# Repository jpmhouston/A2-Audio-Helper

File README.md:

This is a potential Apple II hardware mod I hope to eventually turn into a working physical add-on for any ][, ][+, //e. It’s meant to add these capabilities:

- route sound card audio to the stock speaker
- mixing motherboard audio into the sound card audio (i believe some sound cards don’t come with this feature)
- an optional second speaker mounted into the case for stereo (mounting strategy not determined yet)
- control volume with a knob protruding through a hole dremel'd into case beneath the keyboard (willing to accept feedback about an alternate volume control and placement, of if volume control should be made optional)
- when volume knob turned off, output to a line-out jack at the back of the case (attached to one of those mounts for a //e, not sure what yet for older ][’s)
- output to headphone jack at the back of the case, also controlled by the volume knob, disabling the speaker(s) when connected (also attached to one of those mounts for a //e, maybe both jacks out one wide slot)
- optionally output to another headphone jack at the front of the case (via a second hole in the case beside the volume knob)

These features should be possible using a small circuit board to be mounted within the case beneath the keyboard with some minor modifications, either one or two holes drilled into the case's metal base, the part that's angled upwards. It should require no controller or firmware, and the plan is to connect it to power and ground via the motherboard’s game port (potentially using a pass-through socket to permit its use for joysticks or whatever else). 

The schematic originates from a specification fed to Gemini and a KiCad project created according to its design, making use of a 8403 amplifier module. Needless to say there were numerous back and forth sessions. I created a simple PCB design as a proof of concept, currently all through-hole components. Well it leverages a ready-to-use amplifier module with its own surface-mount components, but that itself needs connection with pin headers.

The latest iteration of the PCB is 4.5cm wide and 6.3cn tall, and I'm hoping they will fit, on a //e between the motherboard and the end of the flat part of the base, somewhat in the center or right of the case. On a ][ / ][+ I'm hoping there's room in front of the power supply. I know the stock speaker is in that area, I'll have to see more 2's in the wild and see. For both models there should also be space at the far right side of the vents for an second speaker to be mounted somehow.

Volume and front headphone are on a small daughterboard, connected via a ribbon cable, that can mount flush to the upwardly angled part of the base, I'm hoping there's room directly under the keyboard at this angle and still allow the knob and jack to be high enough off the table to be useful. The main board however is also able to have the volume and headphone jack populated on it directly instead, for those wanting to mount it with those controls protruding out the side of the case. I'm making it support this just for me really, as my own case if damaged and I don't mind making holes in the beige plastic, and especially if I run into space issues under the keybaord. I suspect this option will be less of an interest to others since making holes in the beige plastic is not something they'd want to do, and not something I'd recommend.

I also am planning how to mount line-out and optionally a second headphone jack to the back of the case. I've found what might be good jack components, and I think they'll work in one of the long //e openings, but not sure yet. I suspect some 3D-printed thing will be involved in making this work.

I'm putting the cart before the horse a bit iterating over the PCB layout and pondering these physical issues, as I’ve still yet to test an implementation of the schematic on a breadboard.

Feedback and assistance are appreciated on the Discussions page for this repo, especially feedback on the schematic and PCB since I really a beginner in all this. Especially feedback on the physical mounting and modding challenges for this thing. Thanks.

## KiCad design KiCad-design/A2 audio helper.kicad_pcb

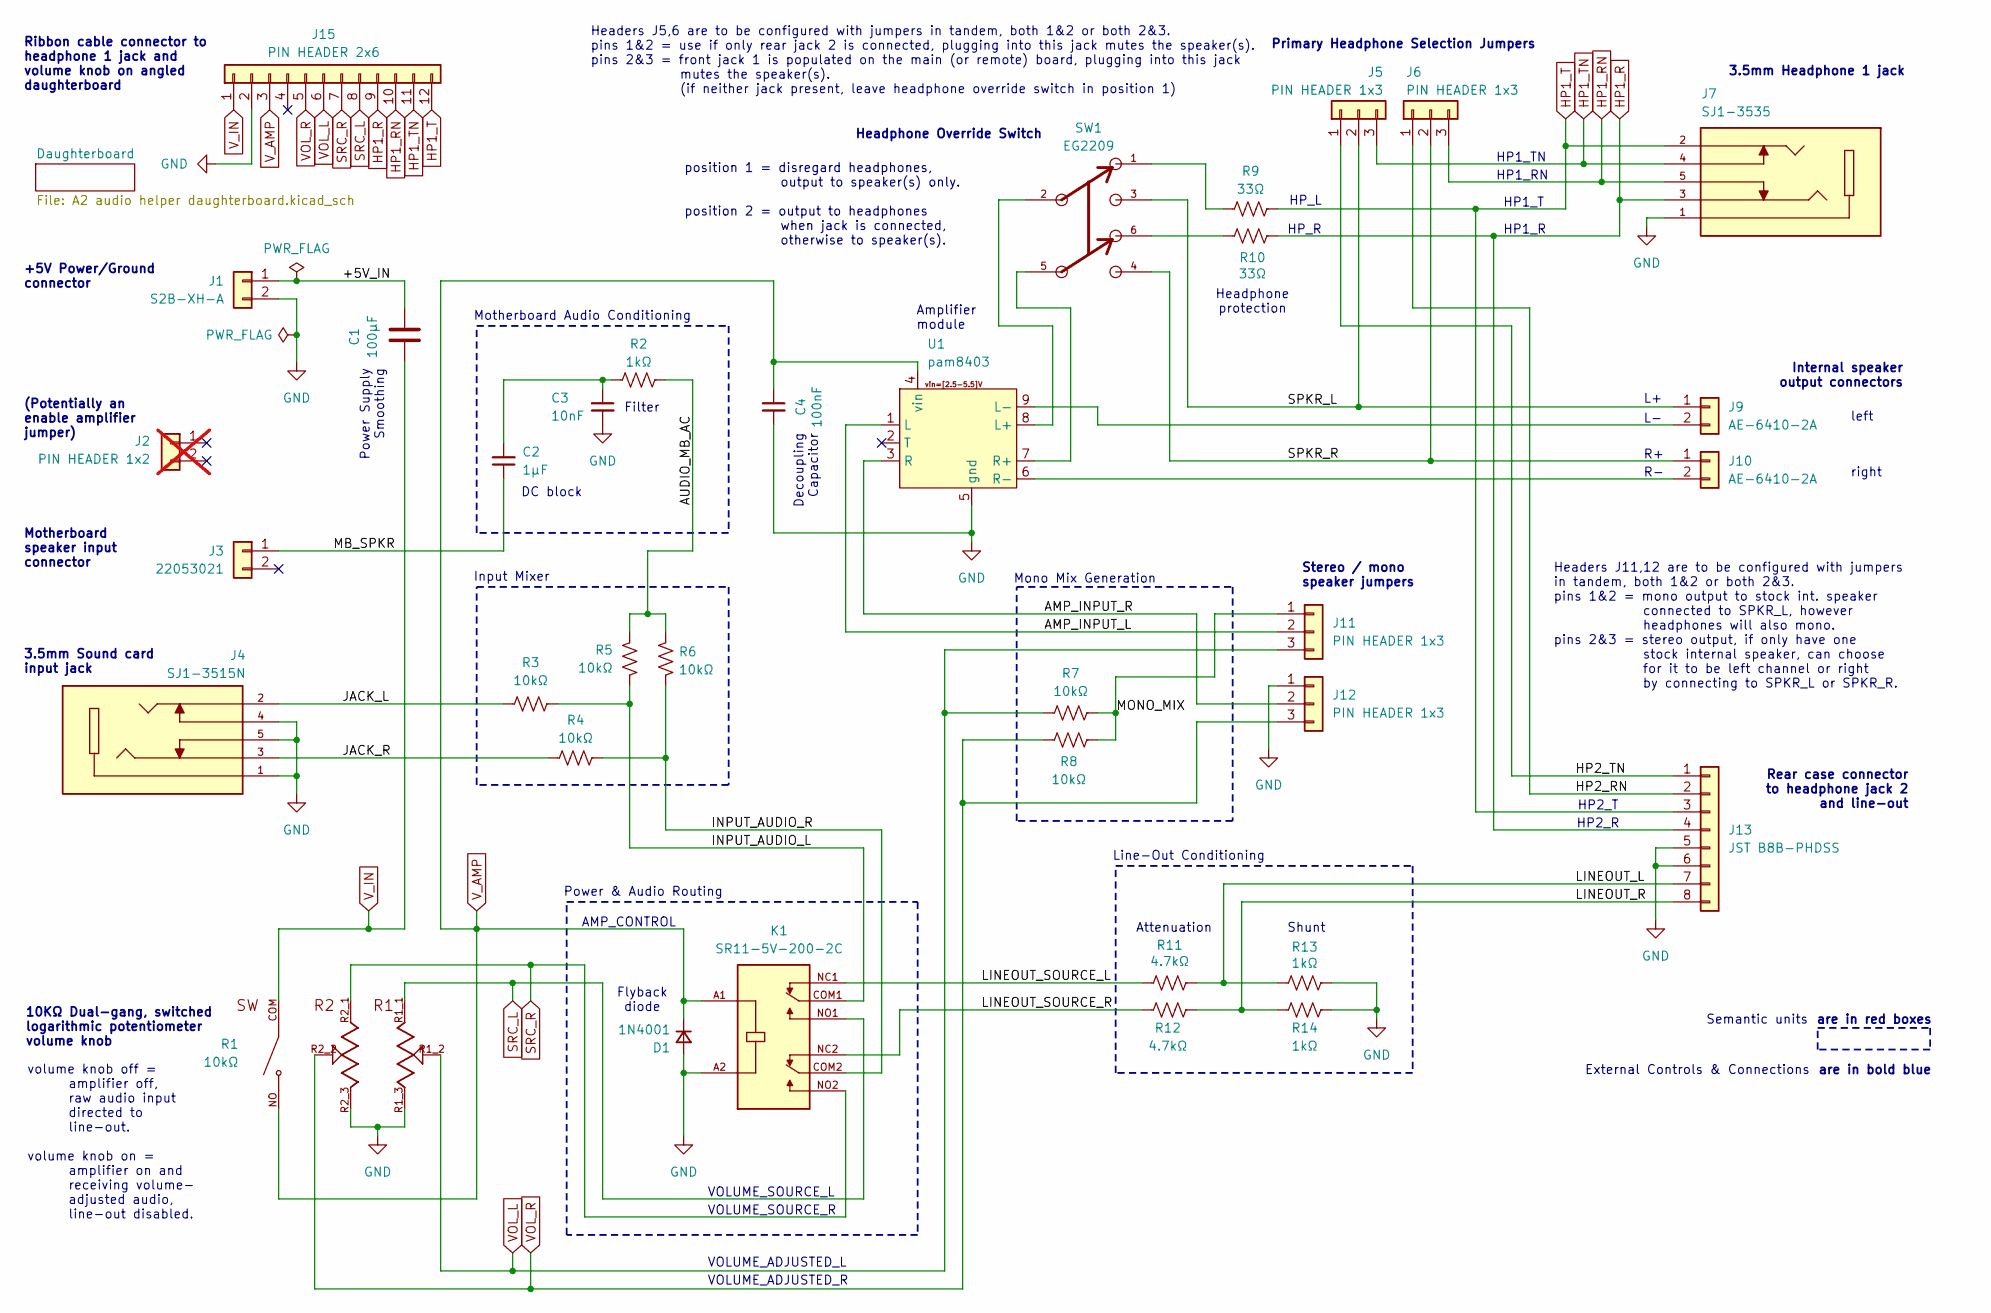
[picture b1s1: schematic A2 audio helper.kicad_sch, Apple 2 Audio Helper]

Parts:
C1: 100µF; C_Radial_D6.3mm_H7.0mm_P2.50mm
C2: 1µF; C_Radial_D5.0mm_H5.0mm_P2.00mm
C3: 10nF; C_Disc_D4.7mm_W2.5mm_P5.00mm
C4: 100nF; C_Disc_D4.7mm_W2.5mm_P5.00mm
D1: 1N4001; D_DO-35_SOD27_P7.62mm_Horizontal
J1: S2B-XH-A; JST_XH_S2B-XH-A_1x02_P2.50mm_Horizontal
J2: PIN HEADER 1x2; PinHeader_1x02_P2.54mm_Vertical; not fitted
J3: 22053021; CONN_A-7478-02A_MOL
J4: SJ1-3515N; CUI_SJ1-3515N; PARTREV 1.03
J5, J6, J11, J12: PIN HEADER 1x3; PinHeader_1x03_P2.54mm_Vertical
J7: SJ1-3535; CUI_SJ1-3535; PARTREV 1.03
J9, J10: AE-6410-2A; Molex_KK-254_AE-6410-02A_1x02_P2.54mm_Vertical
J13: JST B8B-PHDSS; JST_PHD_B8B-PHDSS_2x04_P2.00mm_Vertical
J15: PIN HEADER 2x6; PinSocket_2x06_P2.00mm_Vertical
K1: SR11-5V-200-2C; RELAY_SR11-5V-200-2C; PARTREV 1.01; DigiKey_Part_Number 2223-SR11-5V-200-2C-ND
R1: 10kΩ; TRIM_PTN09S2-H10215K1A; PARTREV 10/19
R2, R13, R14: 1kΩ; R_Axial_DIN0207_L6.3mm_D2.5mm_P10.16mm_Horizontal
R3, R4, R5, R6, R7, R8: 10kΩ; R_Axial_DIN0207_L6.3mm_D2.5mm_P10.16mm_Horizontal
R9, R10: 33Ω; R_Axial_DIN0207_L6.3mm_D2.5mm_P10.16mm_Horizontal
R11, R12: 4.7kΩ; R_Axial_DIN0207_L6.3mm_D2.5mm_P10.16mm_Horizontal
SW1: EG2209
U1: pam8403

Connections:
/+5V_IN: C1.1, J1.1
/AMP_INPUT_L: J11.2, U1.1 (L)
/AMP_INPUT_R: J12.2, U1.3 (R)
/AUDIO_MB_AC: R2.2, R5.1, R6.1
/HP2_RN: J6.1, J13.2
/HP2_TN: J5.1, J13.1
/INPUT_AUDIO_L: K1.COM1, R3.2, R5.2
/INPUT_AUDIO_R: K1.COM2, R4.2, R6.2
/JACK_L: J4.2, R3.1
/JACK_R: J4.3, R4.1
/LINEOUT_L: J13.7, R11.2, R13.1
/LINEOUT_R: J13.8, R12.1, R14.1
/LINEOUT_SOURCE_L: K1.NC1, R11.1
/LINEOUT_SOURCE_R: K1.NC2, R12.2
/MB_SPKR: C2.1, J3.1
/MONO_MIX: J11.1, R7.2, R8.2
/SPKR_L: J5.2, J9.1, SW1.3
/SPKR_R: J6.2, J10.1, SW1.4
GND: C3.2, C4.2, D1.2 (A), J1.2, J4.1, J4.4, J4.5, J7.1, J12.1, J13.5, J13.6, J15.2, K1.A2, R1.R1_3, R1.R2_3, R13.2, R14.2, U1.5 (gnd)
HP1_R: J7.3, J13.4, J15.9, R10.2
HP1_RN: J6.3, J7.5, J15.10
HP1_T: J7.2, J13.3, J15.12, R9.2
HP1_TN: J5.3, J7.4, J15.11
unnamed: C2.2, C3.1, R2.1
unnamed: J9.2, U1.9 (L-)
unnamed: J10.2, U1.6 (R-)
unnamed: R9.1, SW1.1
unnamed: R10.1, SW1.6
unnamed: SW1.2, U1.8 (L+)
unnamed: SW1.5, U1.7 (R+)
SRC_L: J15.8, K1.NO1, R1.R1_1
SRC_R: J15.7, K1.NO2, R1.R2_1
VOL_L: J11.3, J15.6, R1.R1_2, R7.1
VOL_R: J12.3, J15.5, R1.R2_2, R8.1
V_AMP: C4.1, D1.1 (K), J15.3, K1.A1, R1.NO, U1.4 (vin)
V_IN: C1.2, J15.1, R1.COM

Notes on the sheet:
VOLUME_ADJUSTED_R
Headphone Override Switch
3.5mm Sound card input jack
HP2_R
10KΩ Dual-gang, switched logarithmic potentiometer volume knob
Motherboard speaker input connector
HP1_TN
Mono Mix Generation
HP2_T
are in red boxes
AMP_CONTROL
Ribbon cable connector to headphone 1 jack and volume knob on angled daughterboard
Primary Headphone Selection Jumpers
HP1_T
External Controls & Connections
HP_L
Headphone protection
Headers J5,6 are to be configured with jumpers in tandem, both 1&2 or both 2&3. pins 1&2 = use if only rear jack 2 is connected, plugging into this jack mutes the speaker(s). pins 2&3 = front jack 1 is populated on the main (or remote) board, plugging into this jack mutes the speaker(s). (if neithe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
HP1_R
Semantic units
Stereo / mono speaker jumpers
Motherboard Audio Conditioning
DC block
volume knob off = amplifier off, raw audio input directed to line-out. volume knob on = amplifier on and receiving volume- adjusted audio, line-out disabled.
Attenuation
Decoupling Capacitor
Input Mixer
(Potentially an enable amplifier jumper)
VOLUME_SOURCE_R
Rear case connector to headphone jack 2 and line-out
Flyback diode
HP1_RN
position 1 = disregard headphones, output to speaker(s) only. position 2 = output to headphones when jack is connected, otherwise to speaker(s).
VOLUME_ADJUSTED_L
left
HP_R
Shunt
are in bold blue
Filter
Power Supply Smoothing

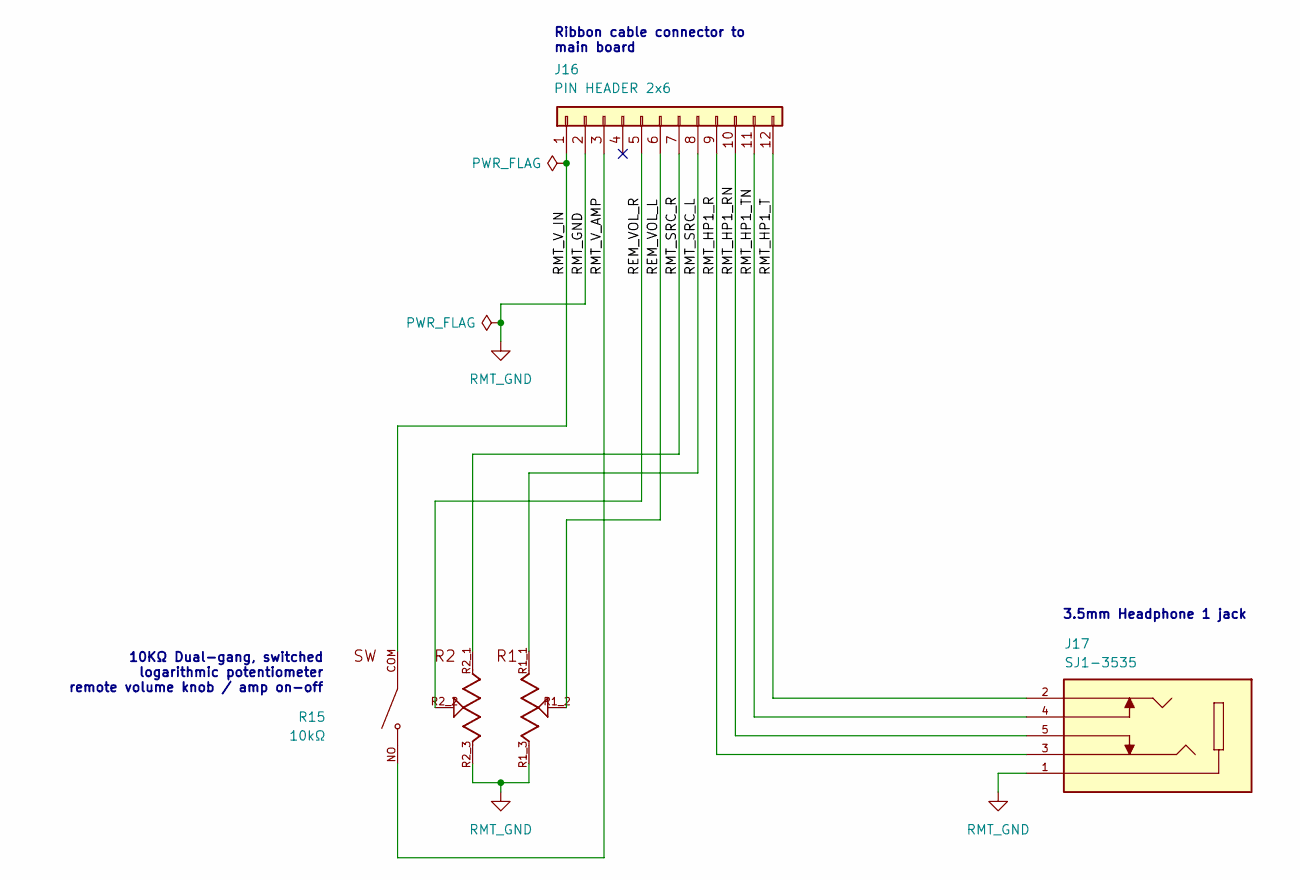
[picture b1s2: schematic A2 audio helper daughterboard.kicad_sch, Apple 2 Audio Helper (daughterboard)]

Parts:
J16: PIN HEADER 2x6; PinSocket_2x06_P2.00mm_Vertical
J17: SJ1-3535; CUI_SJ1-3535; PARTREV 1.03
R15: 10kΩ; TRIM_PTN09S2-H10215K1A; PARTREV 10/19

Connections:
/Daughterboard/REM_VOL_L: J16.6, R15.R1_2
/Daughterboard/REM_VOL_R: J16.5, R15.R2_2
/Daughterboard/RMT_HP1_R: J16.9, J17.3
/Daughterboard/RMT_HP1_RN: J16.10, J17.5
/Daughterboard/RMT_HP1_T: J16.12, J17.2
/Daughterboard/RMT_HP1_TN: J16.11, J17.4
/Daughterboard/RMT_SRC_L: J16.8, R15.R1_1
/Daughterboard/RMT_SRC_R: J16.7, R15.R2_1
/Daughterboard/RMT_V_AMP: J16.3, R15.NO
/Daughterboard/RMT_V_IN: J16.1, R15.COM
RMT_GND: J16.2, J17.1, R15.R1_3, R15.R2_3

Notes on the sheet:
10KΩ Dual-gang, switched logarithmic potentiometer remote volume knob / amp on-off
Ribbon cable connector to main board
3.5mm Headphone 1 jack

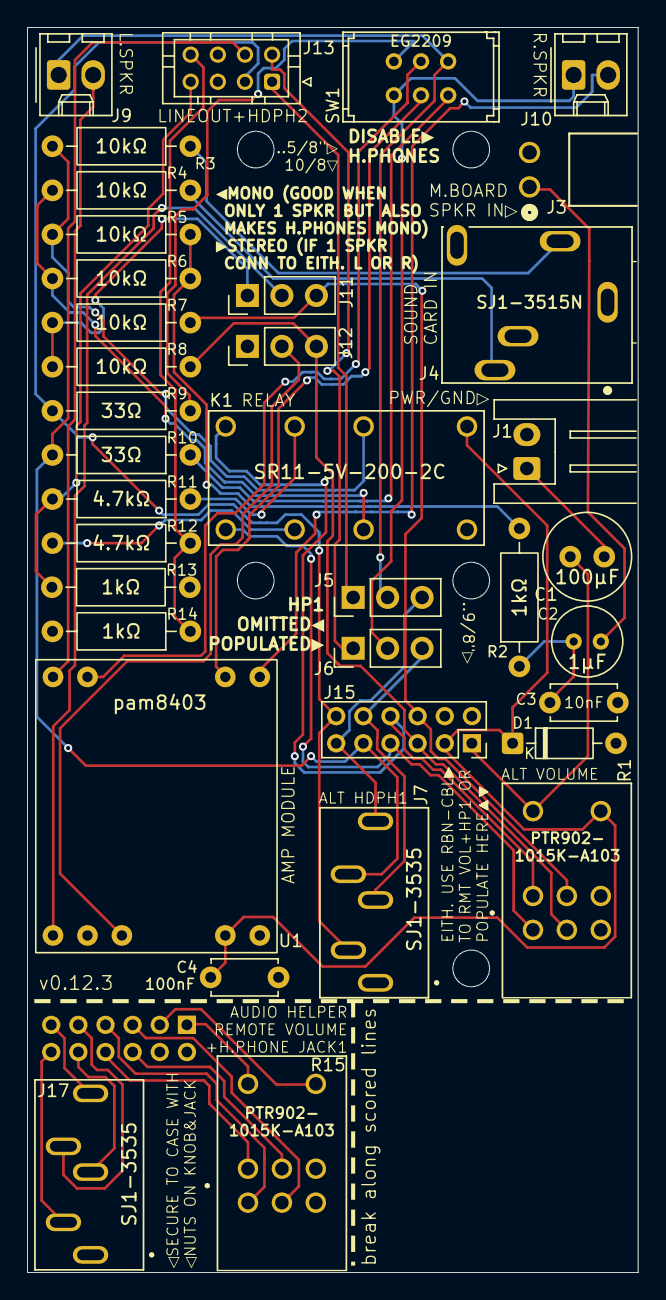
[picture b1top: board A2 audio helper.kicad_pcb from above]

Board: 2 copper layers, 45.0 x 91.8 mm, 37 parts (1 on the bottom side), 47 nets.

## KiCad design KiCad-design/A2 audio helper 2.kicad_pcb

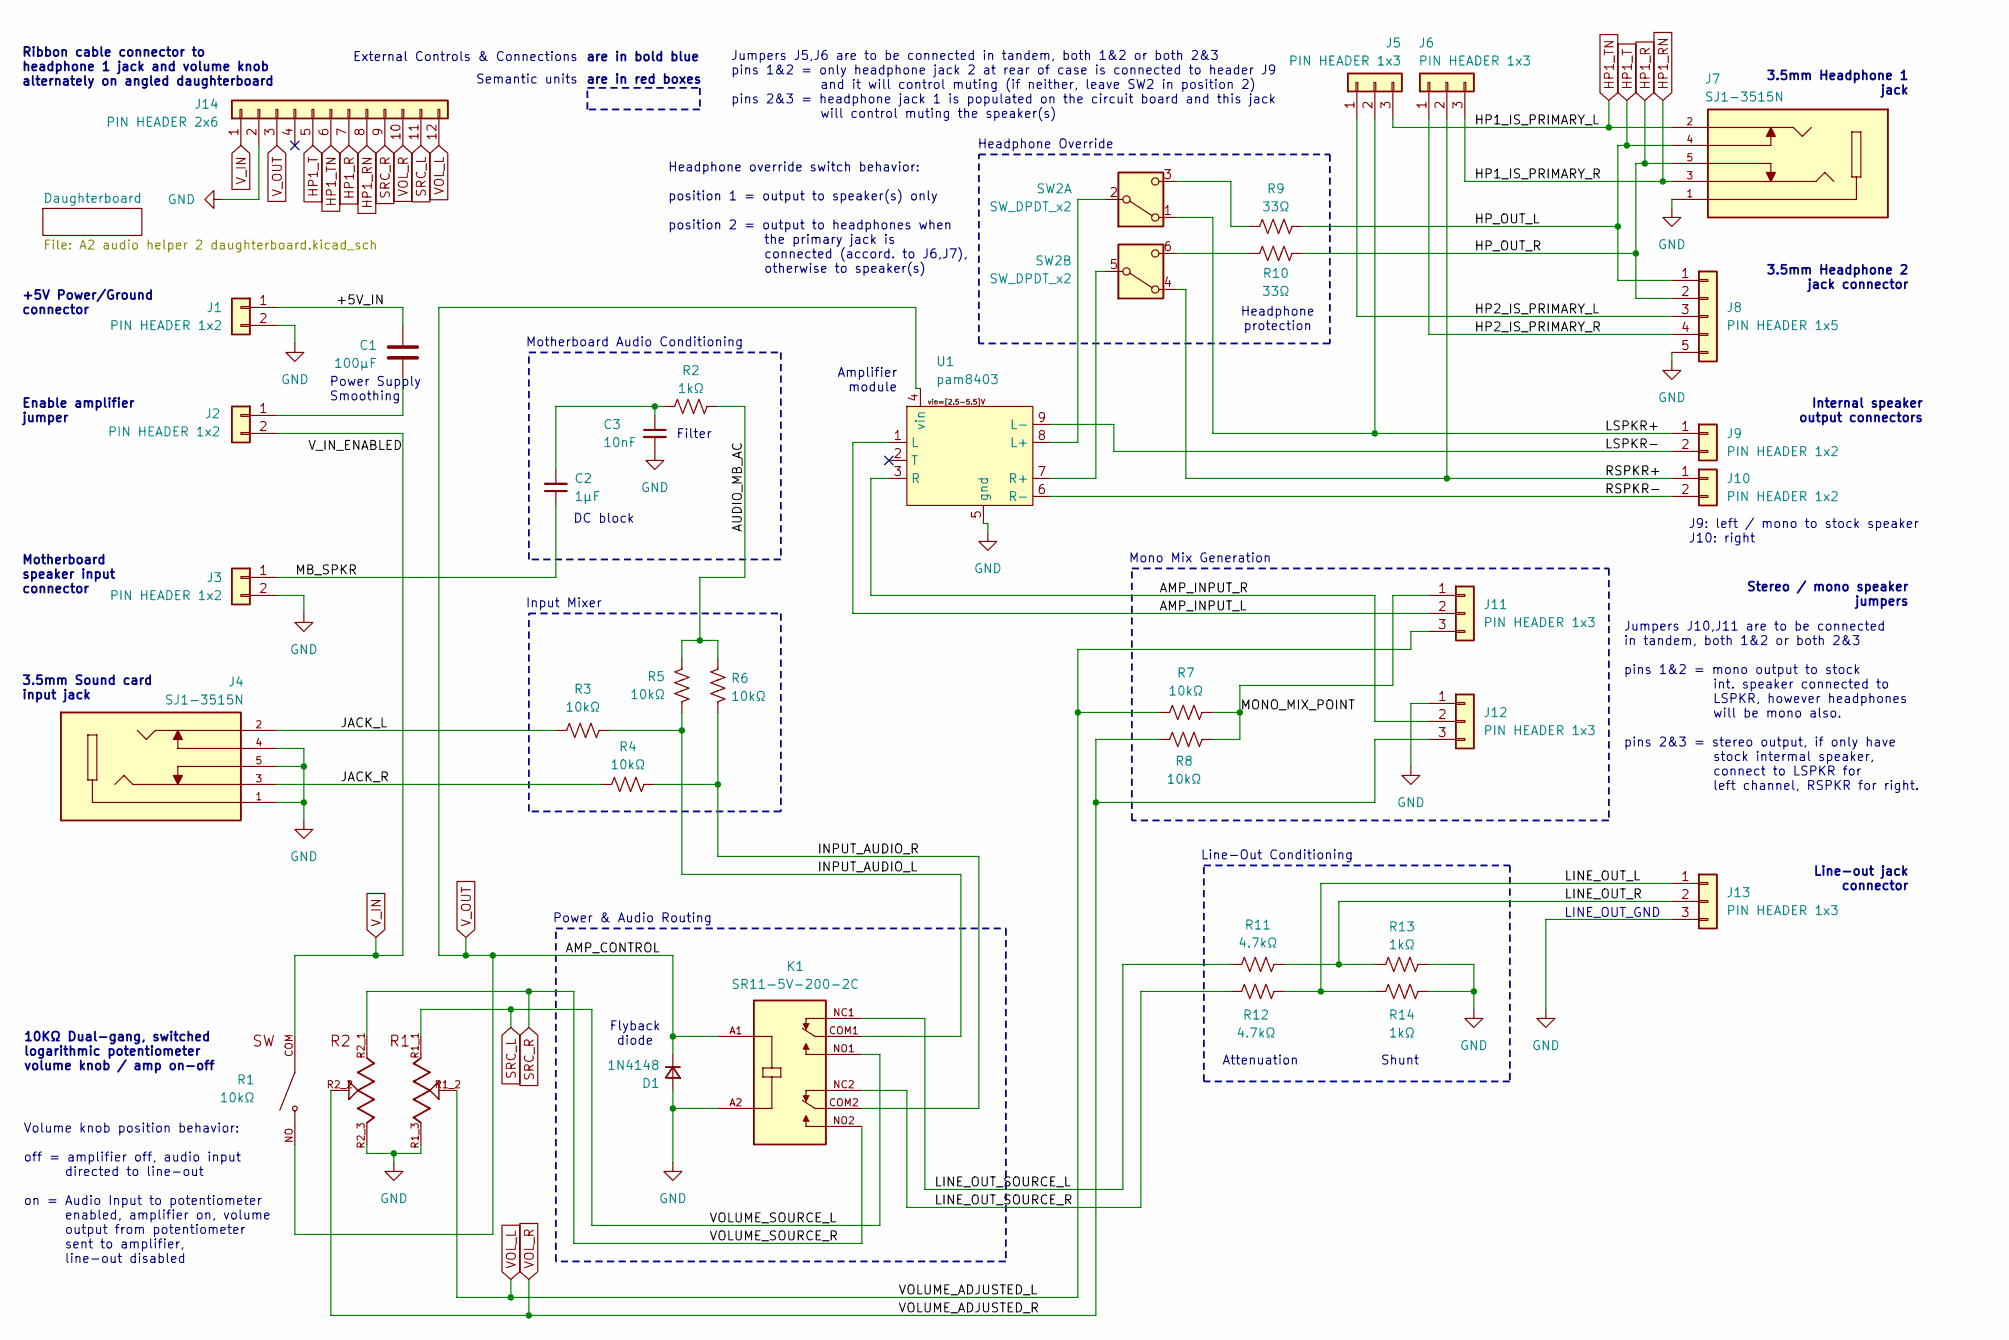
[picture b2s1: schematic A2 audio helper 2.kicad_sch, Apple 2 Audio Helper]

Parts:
C1: 100µF; C_Radial_D6.3mm_H7.0mm_P2.50mm
C2: 1µF; C_Radial_D5.0mm_H5.0mm_P2.00mm
C3: 10nF; C_Disc_D4.7mm_W2.5mm_P5.00mm
D1: 1N4148; D_DO-35_SOD27_P7.62mm_Horizontal
J1: PIN HEADER 1x2; CONN_22035025_MOL
J2: PIN HEADER 1x2; PinHeader_1x02_P2.54mm_Vertical
J3, J9, J10: PIN HEADER 1x2; Molex_KK-254_AE-6410-02A_1x02_P2.54mm_Vertical
J4, J7: SJ1-3515N; CUI_SJ1-3515N; PARTREV 1.03
J5, J6, J11, J12: PIN HEADER 1x3; PinHeader_1x03_P2.54mm_Vertical
J8: PIN HEADER 1x5; Molex_KK-254_AE-6410-05A_1x05_P2.54mm_Vertical
J13: PIN HEADER 1x3; Molex_KK-254_AE-6410-03A_1x03_P2.54mm_Vertical
J14: PIN HEADER 2x6; PinSocket_2x06_P2.00mm_Vertical
K1: SR11-5V-200-2C; RELAY_SR11-5V-200-2C; PARTREV 1.01; DigiKey_Part_Number 2223-SR11-5V-200-2C-ND
R1: 10kΩ; TRIM_PTR902-1020K-A502; PARTREV 10/19
R2, R13, R14: 1kΩ; R_Axial_DIN0207_L6.3mm_D2.5mm_P10.16mm_Horizontal
R3, R4, R5, R6, R7, R8: 10kΩ; R_Axial_DIN0207_L6.3mm_D2.5mm_P10.16mm_Horizontal
R9, R10: 33Ω; R_Axial_DIN0207_L6.3mm_D2.5mm_P10.16mm_Horizontal
R11, R12: 4.7kΩ; R_Axial_DIN0207_L6.3mm_D2.5mm_P10.16mm_Horizontal
SW2: SW_DPDT_x2; SW_CK_JS202011CQN_DPDT_Straight
U1: pam8403

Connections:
/+5V_IN: C1.1, J1.1
/AMP_INPUT_L: J11.2, U1.1 (L)
/AMP_INPUT_R: J12.2, U1.3 (R)
/AUDIO_MB_AC: R2.2, R5.1, R6.1
/HP2_IS_PRIMARY_L: J5.1, J8.3
/HP2_IS_PRIMARY_R: J6.1, J8.4
/INPUT_AUDIO_L: K1.COM1, R3.2, R5.2
/INPUT_AUDIO_R: K1.COM2, R4.2, R6.2
/JACK_L: J4.2, R3.1
/JACK_R: J4.3, R4.1
/LINE_OUT_L: J13.1, R12.1, R14.1
/LINE_OUT_R: J13.2, R11.2, R13.1
/LINE_OUT_SOURCE_L: K1.NC1, R11.1
/LINE_OUT_SOURCE_R: K1.NC2, R12.2
/LSPKR+: J5.2, J9.1, SW2.1 (A)
/LSPKR-: J9.2, U1.9 (L-)
/MB_SPKR: C2.1, J3.1
/MONO_MIX_POINT: J11.1, R7.2, R8.2
/RSPKR+: J6.2, J10.1, SW2.4 (A)
/RSPKR-: J10.2, U1.6 (R-)
GND: C3.2, D1.2 (A), J1.2, J3.2, J4.1, J4.4, J4.5, J7.1, J8.5, J12.1, J13.3, J14.2, K1.A2, R1.R1_3, R1.R2_3, R13.2, R14.2, U1.5 (gnd)
HP1_R: J7.5, J8.2, J14.7, R10.2
HP1_RN: J6.3, J7.3, J14.8
HP1_T: J7.4, J8.1, J14.5, R9.2
HP1_TN: J5.3, J7.2, J14.6
unnamed: C2.2, C3.1, R2.1
unnamed: C1.2, J2.1
unnamed: SW2.2 (B), U1.8 (L+)
unnamed: R9.1, SW2.3 (C)
unnamed: SW2.5 (B), U1.7 (R+)
unnamed: R10.1, SW2.6 (C)
SRC_L: J14.11, K1.NO1, R1.R1_1
SRC_R: J14.9, K1.NO2, R1.R2_1
VOL_L: J11.3, J14.12, R1.R1_2, R7.1
VOL_R: J12.3, J14.10, R1.R2_2, R8.1
V_IN: J2.2, J14.1, R1.COM
V_OUT: D1.1 (K), J14.3, K1.A1, R1.NO, U1.4 (vin)

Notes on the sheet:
Headphone Override
LINE_OUT_GND
3.5mm Sound card input jack
10KΩ Dual-gang, switched logarithmic potentiometer volume knob / amp on-off
Motherboard speaker input connector
Mono Mix Generation
are in red boxes
Ribbon cable connector to headphone 1 jack and volume knob alternately on angled daughterboard
External Controls & Connections
Line-out jack connector
Headphone protection
Jumpers J5,J6 are to be connected in tandem, both 1&2 or both 2&3 pins 1&2 = only headphone jack 2 at rear of case is connected to header J9 and it will control muting (if neither, leave SW2 in position 2) pins 2&3 = headphone jack 1 is populated on the circuit board and this jack will control muti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
Semantic units
Stereo / mono speaker jumpers
Motherboard Audio Conditioning
DC block
Volume knob position behavior: off = amplifier off, audio input directed to line-out on = Audio Input to potentiometer enabled, amplifier on, volume output from potentiometer sent to amplifier, line-out disabled
Attenuation
Input Mixer
Enable amplifier jumper
Flyback diode
Headphone override switch behavior: position 1 = output to speaker(s) only position 2 = output to headphones when the primary jack is connected (accord. to J6,J7), otherwise to speaker(s)
J9: left / mono to stock speaker J10: right
3.5mm Headphone 2 jack connector
Shunt
are in bold blue
Filter
Power Supply Smoothing
3.5mm Headphone 1 jack
+5V Power/Ground connector
Jumpers J10,J11 are to be connected in tandem, both 1&2 or both 2&3 pins 1&2 = mono output to stock int. speaker connected to LSPKR, however headphones will be mono also. pins 2&3 = stereo output, if only have stock intermal speaker, connect to LSPKR for left channel, RSPKR for right.
Line-Out Conditioning
Power & Audio Routing
Amplifier module
Internal speaker output connectors

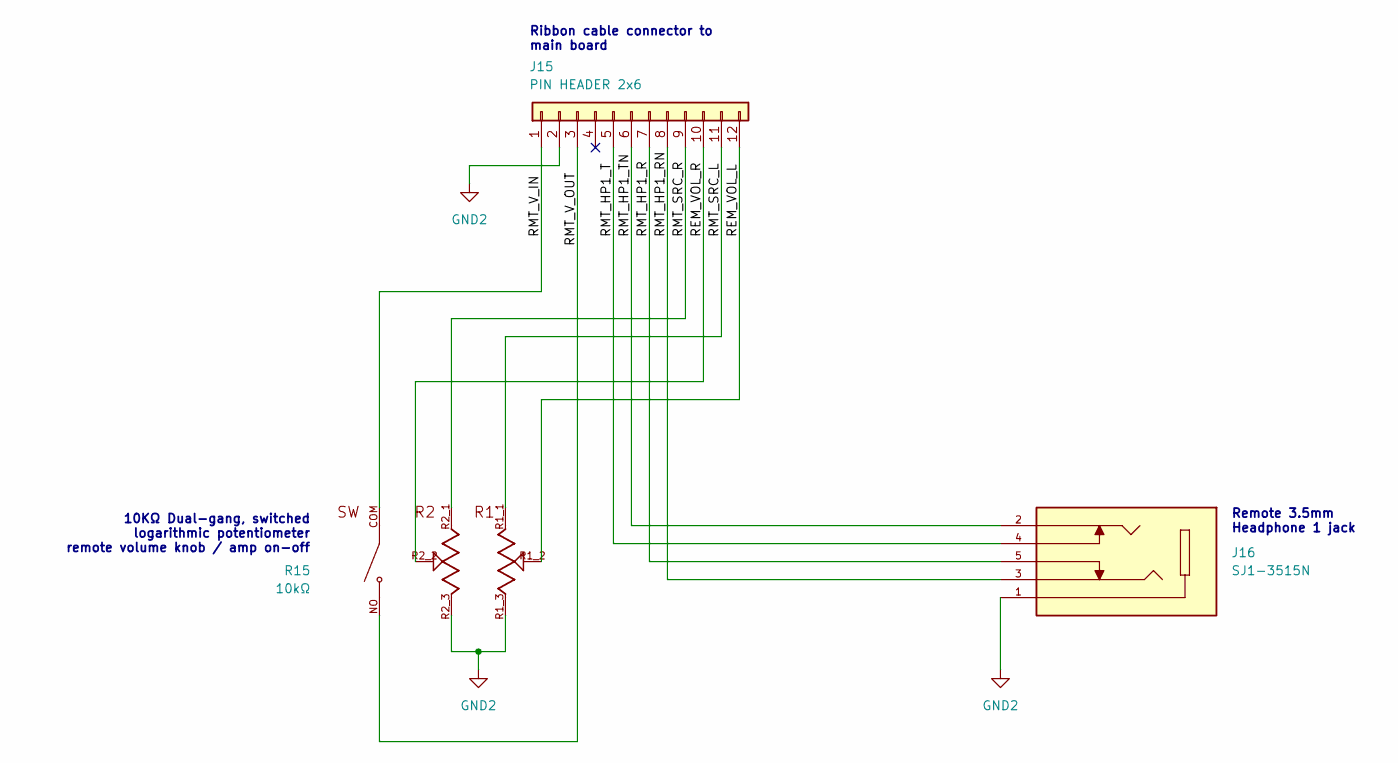
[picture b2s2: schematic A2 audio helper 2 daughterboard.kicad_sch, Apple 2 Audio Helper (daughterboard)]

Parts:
J15: PIN HEADER 2x6; PinSocket_2x06_P2.00mm_Vertical
J16: SJ1-3515N; CUI_SJ1-3515N; PARTREV 1.03
R15: 10kΩ; TRIM_PTR902-1020K-A502; PARTREV 10/19

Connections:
/Daughterboard/REM_VOL_L: J15.12, R15.R1_2
/Daughterboard/REM_VOL_R: J15.10, R15.R2_2
/Daughterboard/RMT_HP1_R: J15.7, J16.5
/Daughterboard/RMT_HP1_RN: J15.8, J16.3
/Daughterboard/RMT_HP1_T: J15.5, J16.4
/Daughterboard/RMT_HP1_TN: J15.6, J16.2
/Daughterboard/RMT_SRC_L: J15.11, R15.R1_1
/Daughterboard/RMT_SRC_R: J15.9, R15.R2_1
/Daughterboard/RMT_V_IN: J15.1, R15.COM
/Daughterboard/RMT_V_OUT: J15.3, R15.NO
GND2: J15.2, J16.1, R15.R1_3, R15.R2_3

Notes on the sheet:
10KΩ Dual-gang, switched logarithmic potentiometer remote volume knob / amp on-off
Remote 3.5mm Headphone 1 jack
Ribbon cable connector to main board

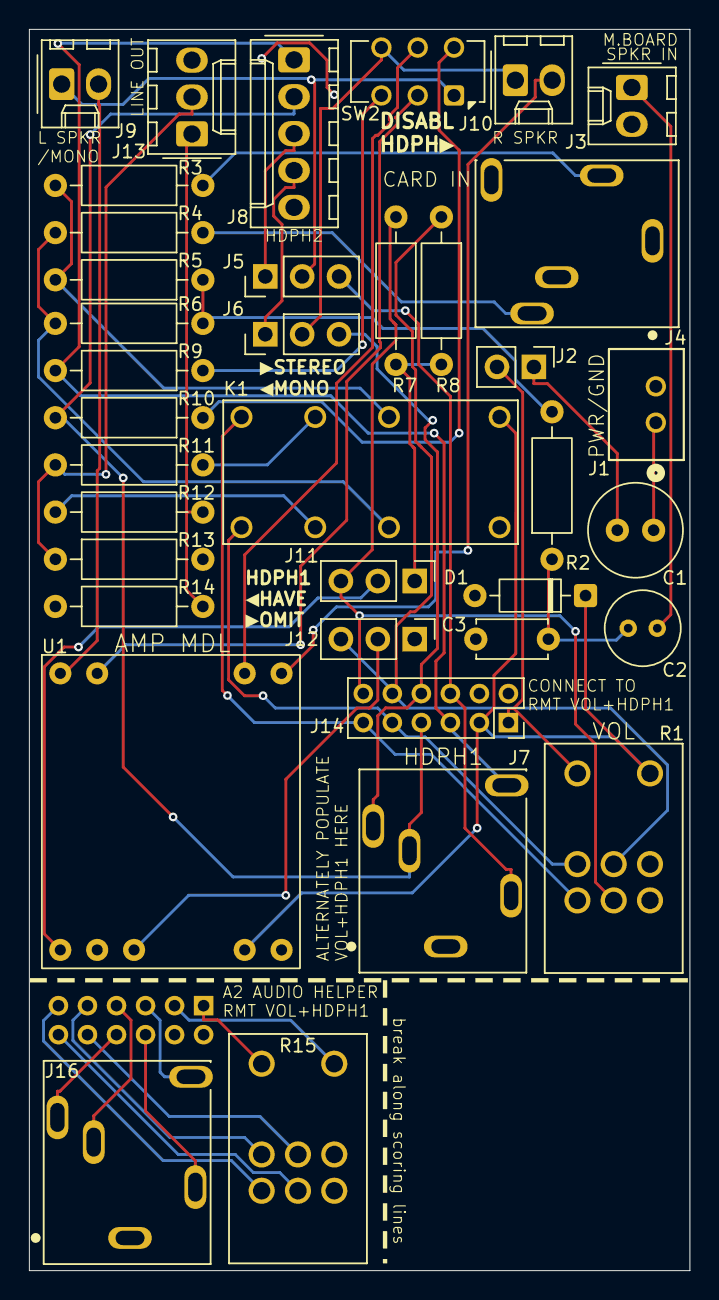
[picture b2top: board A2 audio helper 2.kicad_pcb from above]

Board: 2 copper layers, 45.5 x 85.5 mm, 38 parts (1 on the bottom side), 48 nets.

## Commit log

2026-01-06 add kicad proj with rev 1 of the schematic
2026-01-06 add readme & license
2026-01-09 add guide textfile, revise sc. for simulation WIP
2026-01-10 rename circuit guide, stripping adhoc versioning within its filename
2026-01-10 revision 4 of the guide & schematic
2026-01-10 fixed schematic mistakes & warnings
2026-01-11 fixed schematic issues from sim attempts, better layout
2026-01-12 added 5V smoothing cap, added rear hp jack connector
2026-01-17 syms/footprints, 1st draft pcb
2026-01-18 minor simplification, 1st draft pcb
2026-01-20 picked new connectors, pcb take 2
2026-01-20 ribbon cbl to remote vol & headph board
2026-01-20 ribbon cable part link in guide
2026-01-21 desc'd ribbon conn better in schematic, fixed LSPKR+ error
2026-01-25 daughtercard pcb, for now connected & perforated
2026-01-29 fixed dual headphones
2026-01-30 improved fix for dual headphones
2026-02-01 tweaks to pcb, found vol knob 3dmodel
2026-02-02 combined connector to back of case, lineout & hdph 2
2026-02-07 made power & speaker input connectors also horizontal
2026-02-09 added recommended decoupling cap to amp pwr/gnd
2026-02-19 changed pwr/gnd connector to more common jst connector
2026-02-19 fixed mb spkr pin 2 which isnt ground afterall
2026-02-21 trim some footprints to edges, pos'n consistently
2026-02-26 change 3d model for vol knob
2026-02-27 picked new part for front hp jack
2026-02-28 lengthened, new bigger switch part, cleanup
2026-03-09 pcb mount holes, add missing component files
